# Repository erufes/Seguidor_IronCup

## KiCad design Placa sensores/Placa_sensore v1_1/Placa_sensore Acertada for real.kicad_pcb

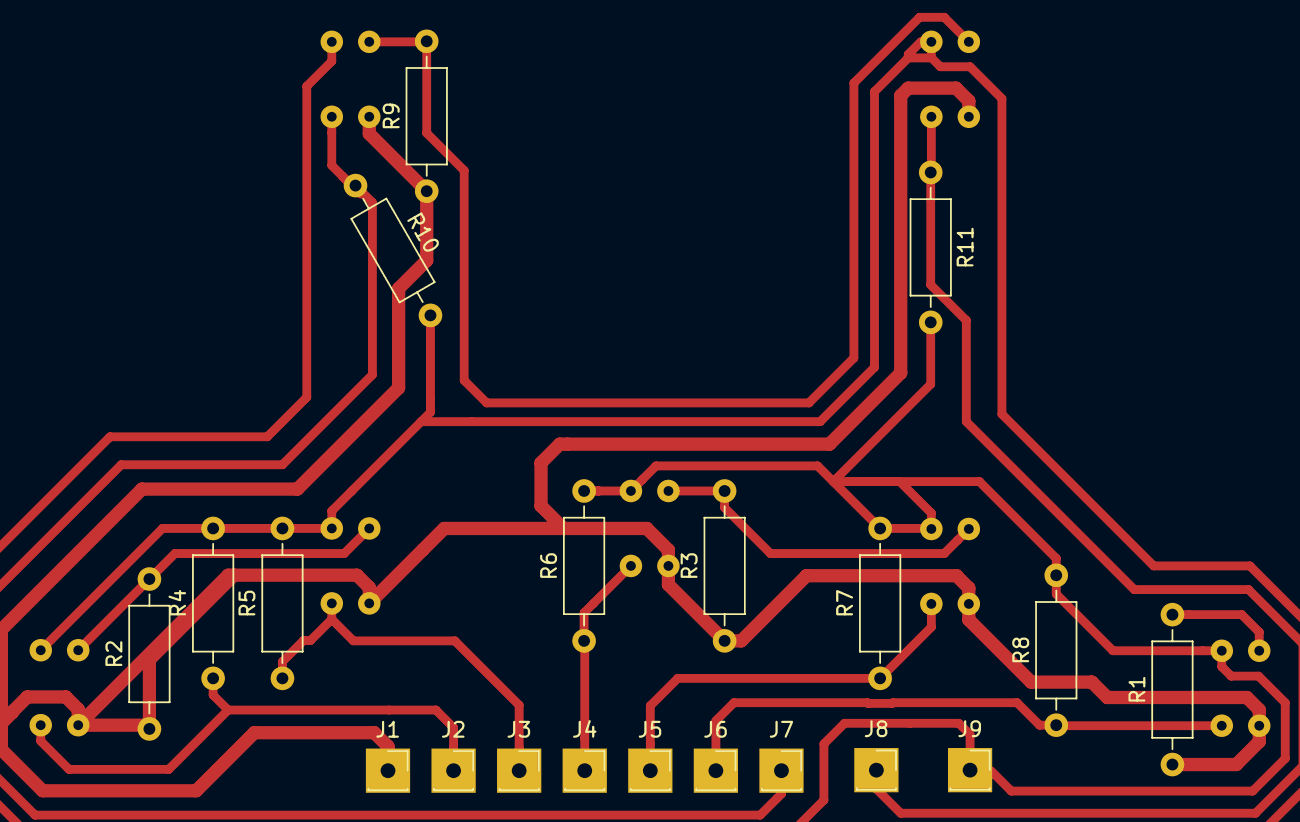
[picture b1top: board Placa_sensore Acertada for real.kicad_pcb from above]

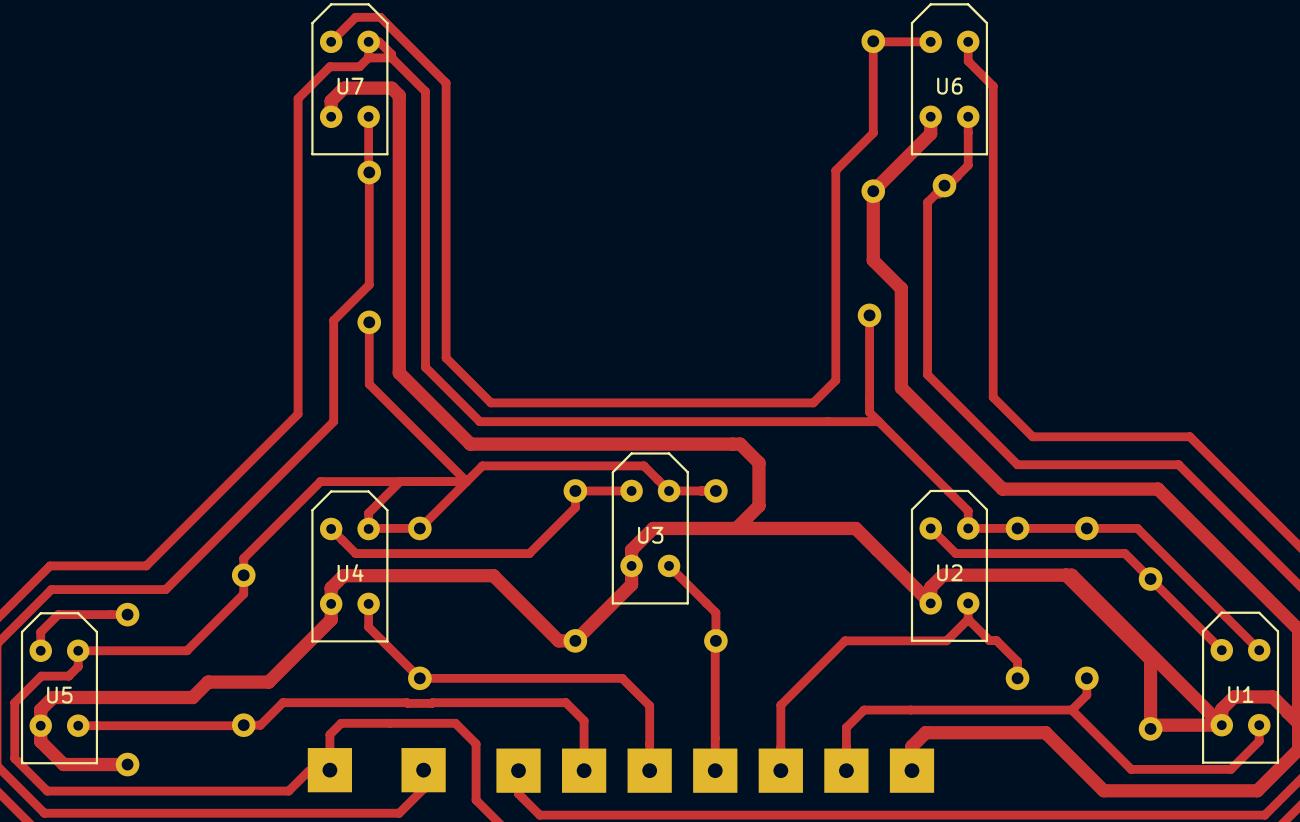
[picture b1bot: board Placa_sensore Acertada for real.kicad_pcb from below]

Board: 2 copper layers, 27 parts (7 on the bottom side), 13 nets.

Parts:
J1, J2, J3, J4, J5, J6, J7, J8, J9: Conn_01x01_Female; PinSocket_1x01_P2.54mm_Vertical
R1, R2, R3, R9: 330; R_Axial_DIN0207_L6.3mm_D2.5mm_P10.16mm_Horizontal
R4, R5, R6, R7, R8, R10, R11: 10k; R_Axial_DIN0207_L6.3mm_D2.5mm_P10.16mm_Horizontal
U1, U2, U3, U4, U5, U6, U7: TCRT5000; TCRT50002

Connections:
GND: J9.1, R4.2, R5.2, R6.2, R7.2, R8.2, R10.2, R11.2, U1.2, U2.2, U3.2, U4.2, U5.2, U6.2, U7.2
unnamed: R1.2, U5.1
unnamed: R2.2, U1.1, U2.1
unnamed: R3.2, U3.1, U4.1
unnamed: R9.2, U6.1, U7.1
S1: J2.1, R4.1, U1.4
S2: J3.1, R5.1, U2.4
S3: J4.1, R6.1, U3.4
S4: J5.1, R7.1, U4.4
S5: J6.1, R8.1, U5.4
S6: J7.1, R10.1, U6.4
S7: J8.1, R11.1, U7.4
VCC: J1.1, R1.1, R2.1, R3.1, R9.1, U1.3, U2.3, U3.3, U4.3, U5.3, U6.3, U7.3
